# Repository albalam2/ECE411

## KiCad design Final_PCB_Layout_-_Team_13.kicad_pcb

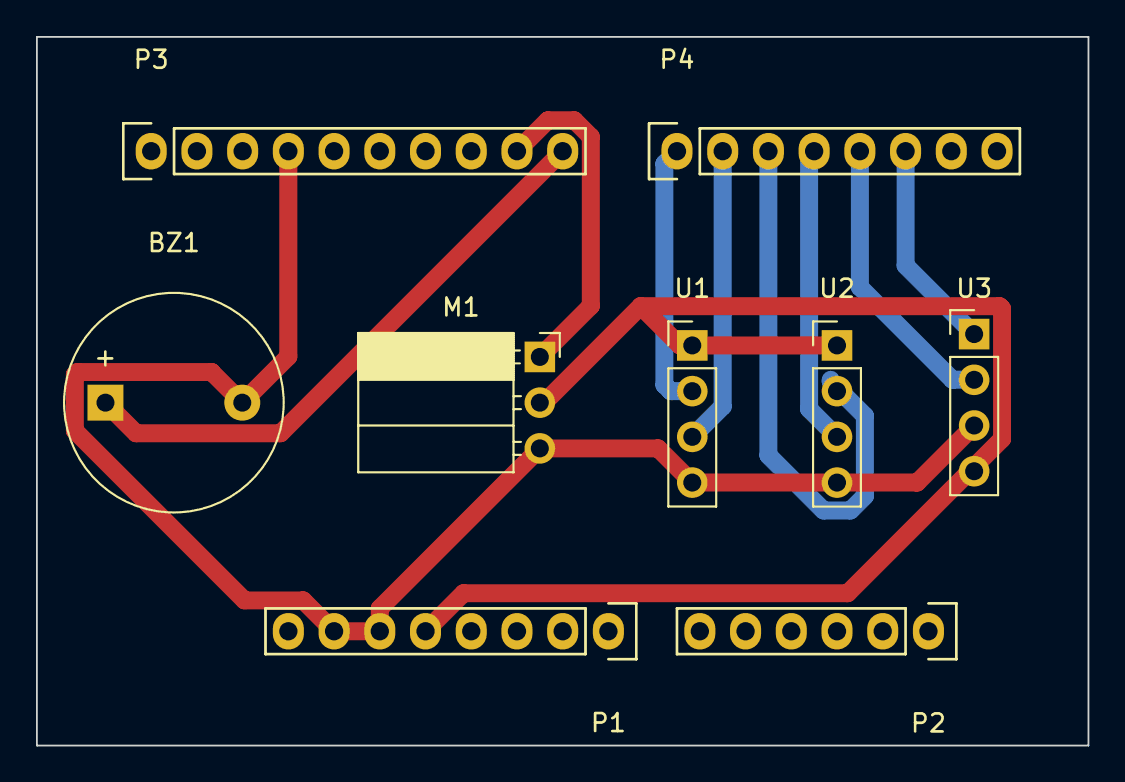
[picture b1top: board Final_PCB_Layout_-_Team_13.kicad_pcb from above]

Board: 2 copper layers, 58.4 x 39.4 mm, 9 parts (0 on the bottom side), 10 nets.

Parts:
BZ1: Buzzer; Buzzer_12x9.5RM7.6
M1: Motor_Servo; PinSocket_1x03_P2.54mm_Horizontal
P1: Power; Socket_Strip_Arduino_1x08
P2: Analog; Socket_Strip_Arduino_1x06
P3: Digital; Socket_Strip_Arduino_1x10
P4: Digital; Socket_Strip_Arduino_1x08
U1, U2: Ultrasonic; PinHeader_1x04_P2.54mm_Vertical
U3: 5463BW; PinHeader_1x04_P2.54mm_Vertical

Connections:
+5V: M1.2, P1.5, U1.1, U2.1, U3.4
/2: P4.6, U3.1
/3(**): P4.5, U3.2
/4: P4.4, U2.3
/5(**): P4.3, U2.2
/6(**): P4.2, U1.3
/7: P4.1, U1.2
/8: BZ1.1, P3.10
/9(**): M1.1, P3.9
GND: BZ1.2, M1.3, P1.6, P1.7, P3.4, U1.4, U2.4, U3.3
